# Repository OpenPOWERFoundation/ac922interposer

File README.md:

# ac922interposer

The purpose of this design is to enable the AC922 to accept a DC-SCM v1.0 hardware management module.  This enables a developement
platform for software development.

For connection with a DC-SCM, the DC-SCM v1.0 release design specifies the connector as an SFF-TA-1002 compliant 4C+ connector. The 4C+ connector is a 4C compliant connector with an additional 28-pin “OCP bay” defined in the OCP NIC 3.0 specification.  The right-angled variety allows for the DC-SCM to lay within the BMC cage assembly.  This can be implemented with TE 2336568-1.

References:

DC-SCM 0.95 Draft Specification:
https://www.opencompute.org/documents/ocp-dc-scm-spec-rev-0-95-pdf

DC-SCM 2.0 Draft Specification:
https://drive.google.com/file/d/1UkFgAFKh8qz4mAXdvodYsW0fg8XhyVf2/view?usp=sharing

AC922 Specification:
see OpenPower website

SFF-TA-1002 Protocol Agnostic Multi-Lane High Speed Connector
https://members.snia.org/document/dl/27231

AntMicro Design Specification:
https://github.com/antmicro/artix-dc-scm.git

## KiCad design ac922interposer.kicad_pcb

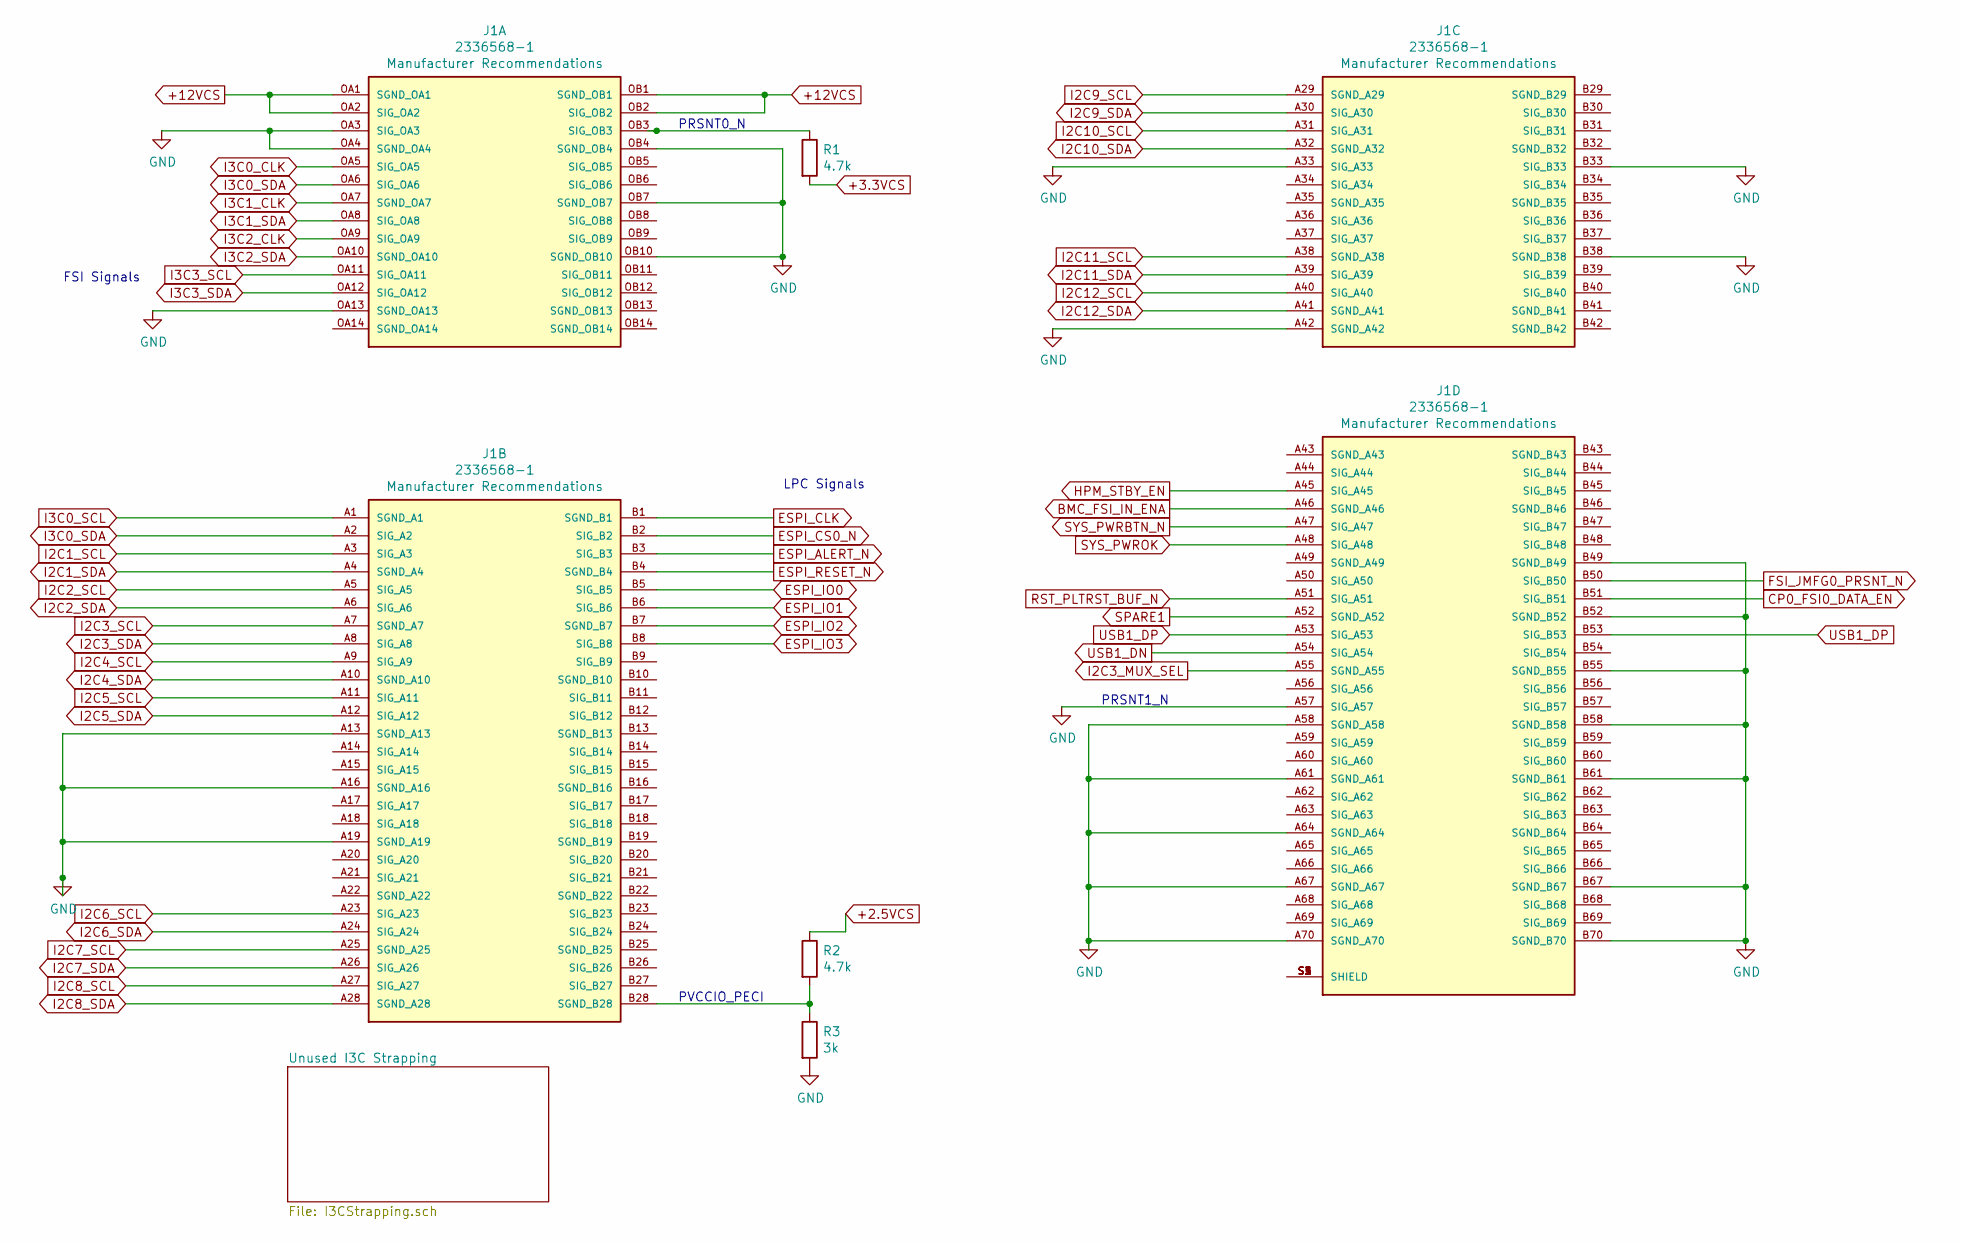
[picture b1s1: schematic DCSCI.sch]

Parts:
J1: 2336568-1; TE_2336568-1; PARTREV A
R1, R2: 4.7k; R_0805_2012Metric
R3: 3k; R_0805_2012Metric

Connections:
+3.3VCS: R1.2; also elsewhere on the board
+12VCS: J1.OA1 (SGND_OA1), J1.OA2 (SIG_OA2), J1.OB1 (SGND_OB1), J1.OB2 (SIG_OB2); also elsewhere on the board
BMC_FSI_IN_ENA: J1.A46 (SGND_A46); also elsewhere on the board
CP0_FSI0_DATA_EN: J1.B51 (SIG_B51); also elsewhere on the board
ESPI_ALERT_N: J1.B3 (SIG_B3); also elsewhere on the board
ESPI_CLK: J1.B1 (SGND_B1); also elsewhere on the board
ESPI_CS0_N: J1.B2 (SIG_B2); also elsewhere on the board
ESPI_IO1: J1.B6 (SIG_B6); also elsewhere on the board
ESPI_IO2: J1.B7 (SGND_B7); also elsewhere on the board
ESPI_IO3: J1.B8 (SIG_B8); also elsewhere on the board
ESPI_RESET_N: J1.B4 (SGND_B4); also elsewhere on the board
FSI_JMFG0_PRSNT_N: J1.B50 (SIG_B50); also elsewhere on the board
HPM_STBY_EN: J1.A45 (SIG_A45); also elsewhere on the board
I2C1_SCL: J1.A3 (SIG_A3); also elsewhere on the board
I2C1_SDA: J1.A4 (SGND_A4); also elsewhere on the board
I2C2_SCL: J1.A5 (SIG_A5); also elsewhere on the board
I2C2_SDA: J1.A6 (SIG_A6); also elsewhere on the board
I2C3_MUX_SEL: J1.A55 (SGND_A55); also elsewhere on the board
I2C3_SCL: J1.A7 (SGND_A7); also elsewhere on the board
I2C3_SDA: J1.A8 (SIG_A8); also elsewhere on the board
I2C4_SCL: J1.A9 (SIG_A9); also elsewhere on the board
I2C4_SDA: J1.A10 (SGND_A10); also elsewhere on the board
I2C5_SCL: J1.A11 (SIG_A11); also elsewhere on the board
I2C5_SDA: J1.A12 (SIG_A12); also elsewhere on the board
I2C6_SCL: J1.A23 (SIG_A23); also elsewhere on the board
I2C6_SDA: J1.A24 (SIG_A24); also elsewhere on the board
I2C7_SCL: J1.A25 (SGND_A25)
I2C7_SDA: J1.A26 (SIG_A26)
I2C8_SCL: J1.A27 (SIG_A27)
I2C8_SDA: J1.A28 (SGND_A28)
I2C9_SCL: J1.A29 (SGND_A29)
I2C9_SDA: J1.A30 (SIG_A30)
I2C10_SCL: J1.A31 (SIG_A31); also elsewhere on the board
I2C10_SDA: J1.A32 (SGND_A32); also elsewhere on the board
I2C11_SCL: J1.A38 (SGND_A38); also elsewhere on the board
I2C11_SDA: J1.A39 (SIG_A39); also elsewhere on the board
I2C12_SCL: J1.A40 (SIG_A40); also elsewhere on the board
I2C12_SDA: J1.A41 (SGND_A41); also elsewhere on the board
I3C0_CLK: J1.OA5 (SIG_OA5); also elsewhere on the board
I3C0_SCL: J1.A1 (SGND_A1)
I3C0_SDA: J1.A2 (SIG_A2), J1.OA6 (SIG_OA6); also elsewhere on the board
I3C1_CLK: J1.OA7 (SGND_OA7); also elsewhere on the board
I3C1_SDA: J1.OA8 (SIG_OA8); also elsewhere on the board
I3C2_CLK: J1.OA9 (SIG_OA9); also elsewhere on the board
I3C2_SDA: J1.OA10 (SGND_OA10); also elsewhere on the board
I3C3_SCL: J1.OA11 (SIG_OA11); also elsewhere on the board
I3C3_SDA: J1.OA12 (SIG_OA12); also elsewhere on the board
unnamed: J1.B28 (SGND_B28), R2.2, R3.1
unnamed: J1.OB3 (SIG_OB3), R1.1
unnamed: J1.S1 (SHIELD), J1.S2 (SHIELD), J1.S3 (SHIELD), J1.S4 (SHIELD), J1.S5 (SHIELD)
RST_PLTRST_BUF_N: J1.A51 (SIG_A51); also elsewhere on the board
SPARE1: J1.A52 (SGND_A52); also elsewhere on the board
SYS_PWRBTN_N: J1.A47 (SIG_A47); also elsewhere on the board
SYS_PWROK: J1.A48 (SIG_A48); also elsewhere on the board
USB1_DN: J1.A54 (SIG_A54); also elsewhere on the board
USB1_DP: J1.A53 (SIG_A53), J1.B53 (SIG_B53); also elsewhere on the board

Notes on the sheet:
LPC Signals
FSI Signals
PRSNT1_N
PRSNT0_N
PVCCIO_PECI

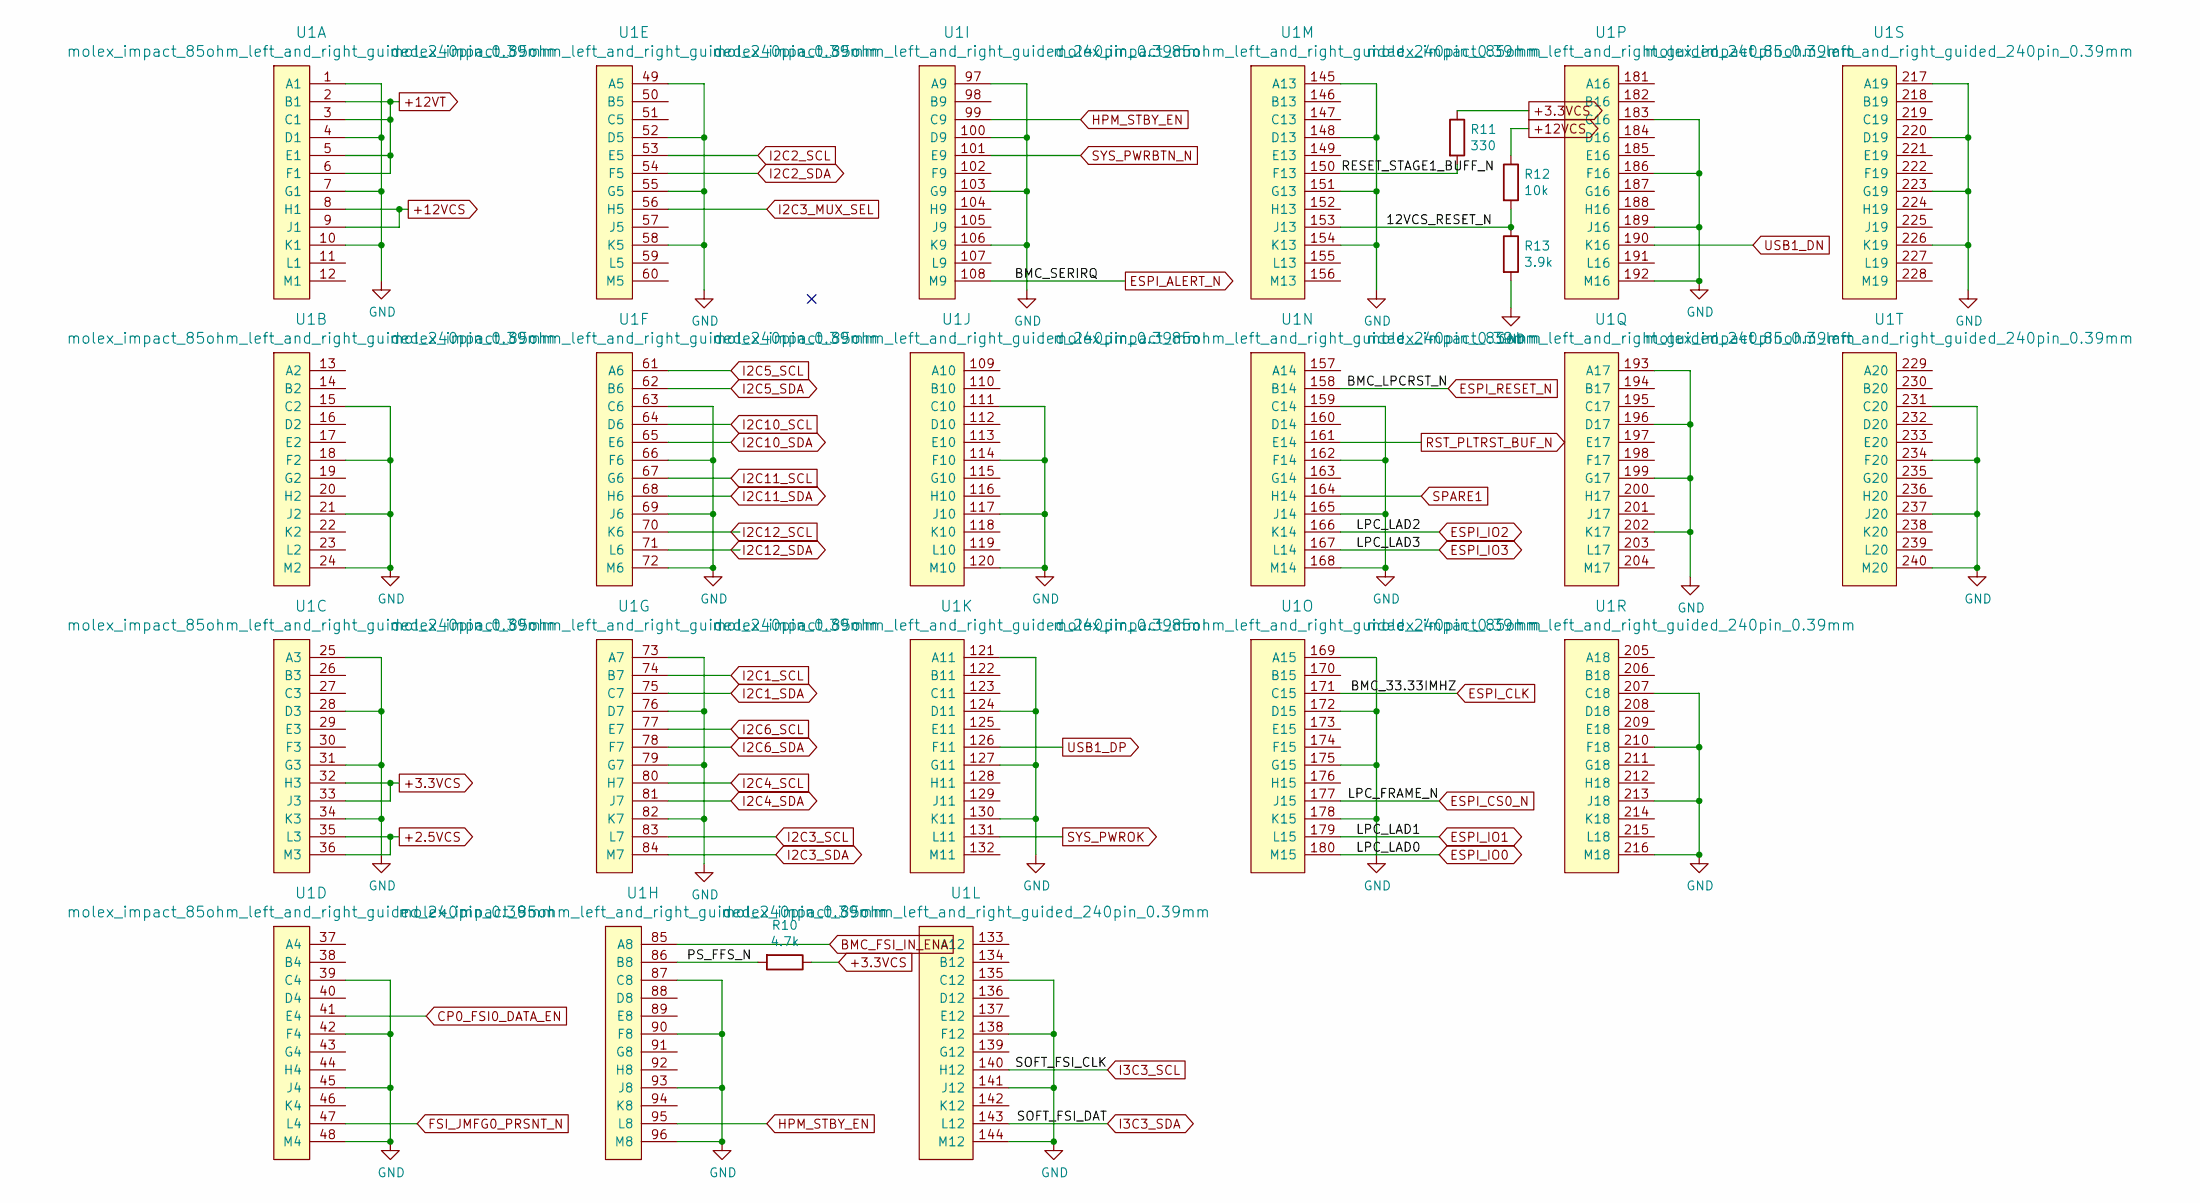
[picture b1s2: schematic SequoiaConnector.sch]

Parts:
R10: 4.7k; R_0805_2012Metric
R11: 330; R_0805_2012Metric
R12: 10k; R_0805_2012Metric
R13: 3.9k; R_0805_2012Metric
U1: molex_impact_85ohm_left_and_right_guided_240pin_0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; molex_impact_85_ohm_left_and_right_guided_240

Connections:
+3.3VCS: R10.1, R11.1, U1.32 (H3), U1.33 (J3); also elsewhere on the board
+12VCS: R12.1, U1.8 (H1), U1.9 (J1); also elsewhere on the board
+12VT: U1.2 (B1), U1.3 (C1), U1.5 (E1), U1.6 (F1)
/Sequoia Connections/12VCS_RESET_N: R12.2, R13.1, U1.153 (J13)
/Sequoia Connections/PS_FFS_N: R10.2, U1.86 (B8)
/Sequoia Connections/RESET_STAGE1_BUFF_N: R11.2, U1.150 (F13)
BMC_FSI_IN_ENA: U1.85 (A8); also elsewhere on the board
CP0_FSI0_DATA_EN: U1.41 (E4); also elsewhere on the board
ESPI_ALERT_N: U1.108 (M9); also elsewhere on the board
ESPI_CLK: U1.171 (C15); also elsewhere on the board
ESPI_CS0_N: U1.177 (J15); also elsewhere on the board
ESPI_IO1: U1.179 (L15); also elsewhere on the board
ESPI_IO2: U1.166 (K14); also elsewhere on the board
ESPI_IO3: U1.167 (L14); also elsewhere on the board
ESPI_RESET_N: U1.158 (B14); also elsewhere on the board
FSI_JMFG0_PRSNT_N: U1.47 (L4); also elsewhere on the board
HPM_STBY_EN: U1.95 (L8), U1.99 (C9); also elsewhere on the board
I2C1_SCL: U1.74 (B7); also elsewhere on the board
I2C1_SDA: U1.75 (C7); also elsewhere on the board
I2C2_SCL: U1.53 (E5); also elsewhere on the board
I2C2_SDA: U1.54 (F5); also elsewhere on the board
I2C3_MUX_SEL: U1.56 (H5); also elsewhere on the board
I2C3_SCL: U1.83 (L7); also elsewhere on the board
I2C3_SDA: U1.84 (M7); also elsewhere on the board
I2C4_SCL: U1.80 (H7); also elsewhere on the board
I2C4_SDA: U1.81 (J7); also elsewhere on the board
I2C5_SCL: U1.61 (A6); also elsewhere on the board
I2C5_SDA: U1.62 (B6); also elsewhere on the board
I2C6_SCL: U1.77 (E7); also elsewhere on the board
I2C6_SDA: U1.78 (F7); also elsewhere on the board
I2C10_SCL: U1.64 (D6); also elsewhere on the board
I2C10_SDA: U1.65 (E6); also elsewhere on the board
I2C11_SCL: U1.67 (G6); also elsewhere on the board
I2C11_SDA: U1.68 (H6); also elsewhere on the board
I2C12_SCL: U1.70 (K6); also elsewhere on the board
I2C12_SDA: U1.71 (L6); also elsewhere on the board
I3C3_SCL: U1.140 (H12); also elsewhere on the board
I3C3_SDA: U1.143 (L12); also elsewhere on the board
RST_PLTRST_BUF_N: U1.161 (E14); also elsewhere on the board
SPARE1: U1.164 (H14); also elsewhere on the board
SYS_PWRBTN_N: U1.101 (E9); also elsewhere on the board
SYS_PWROK: U1.131 (L11); also elsewhere on the board
USB1_DN: U1.190 (K16); also elsewhere on the board
USB1_DP: U1.126 (F11); also elsewhere on the board

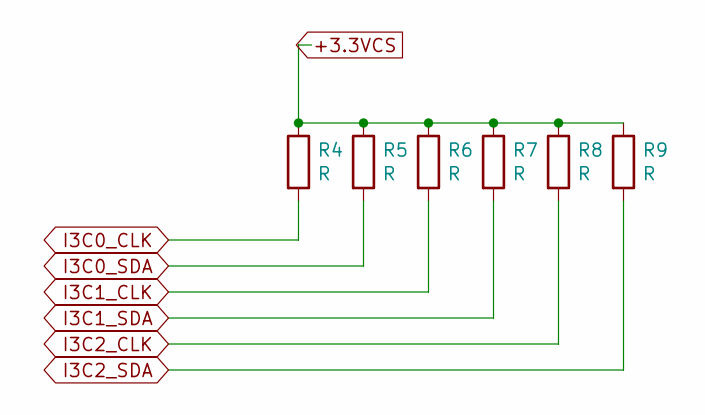
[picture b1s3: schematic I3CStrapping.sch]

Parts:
R4, R5, R6, R7, R8, R9: R; R_0805_2012Metric

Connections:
I3C0_CLK: R4.2; also elsewhere on the board
I3C0_SDA: R5.2; also elsewhere on the board
I3C1_CLK: R6.2; also elsewhere on the board
I3C1_SDA: R7.2; also elsewhere on the board
I3C2_CLK: R8.2; also elsewhere on the board
I3C2_SDA: R9.2; also elsewhere on the board
unnamed: R4.1, R5.1, R6.1, R7.1, R8.1, R9.1

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
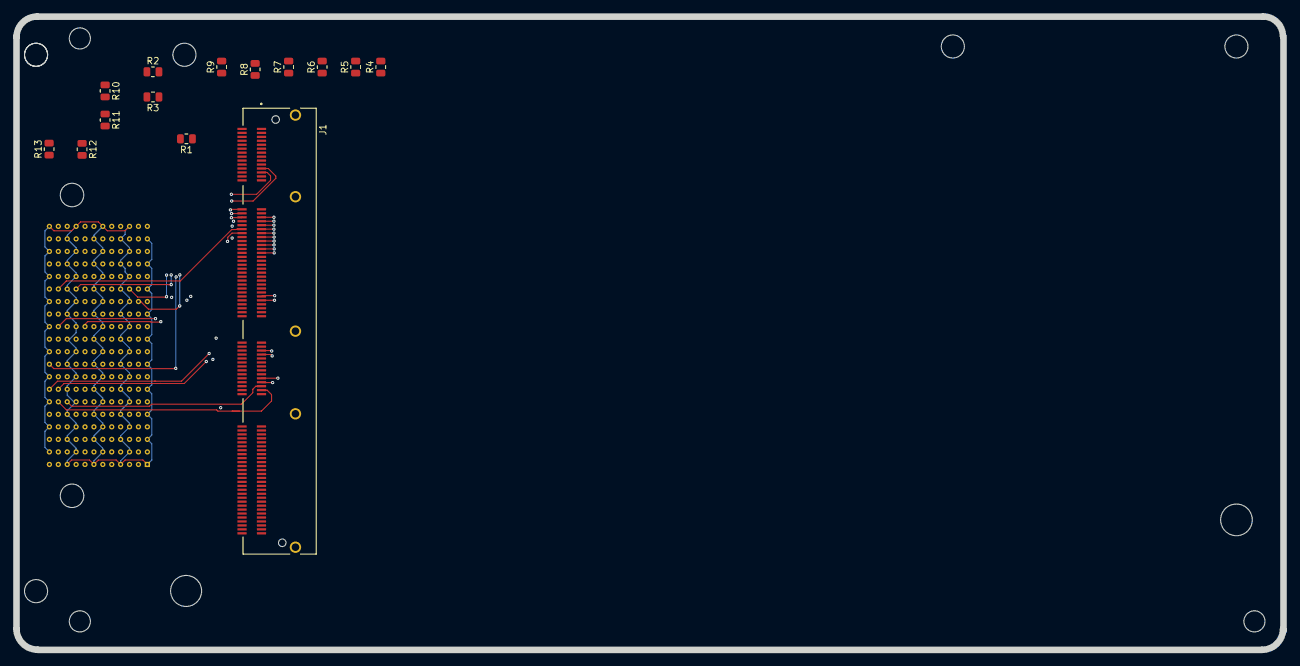
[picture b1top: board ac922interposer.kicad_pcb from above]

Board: 6 copper layers, 192.1 x 96.0 mm, 15 parts (1 on the bottom side), 57 nets.

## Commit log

2021-04-14 initial schematic
2021-04-19 Removed extra junctions that were shorting 2.5v to gnd.
2021-04-20 Placement, initial holes, and some traces.
2021-04-20 Update LICENSE
2021-04-20 Changed license
2021-04-27 Update some routes. Perhaps some schematic.
2021-05-01 first schematic review and first routing
2021-06-05 Design clean, reviewed, and issued to Fab at JLCPCB.
2022-03-29 Interposer 240pin connector pinout
2022-04-12 240pin connector pinout
2022-04-12 Delete '240pin connector pinout.docx
    This needs to be in plain txt, not docx. I added the plain text version and am now deleting the .docx version.
2022-04-18 Correct 240pin for BMC card (aka Boxelder)
    Note the connector is actually split into 2 with a left and right half -- each containing 120pins. If the pin reference is blank, then the pin is a NC.
2022-04-18 This was a very old and incorrect pinout
2022-08-10 Add .gitattributes

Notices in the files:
ac922interposer.kicad_pcb:
License: The MIT License
